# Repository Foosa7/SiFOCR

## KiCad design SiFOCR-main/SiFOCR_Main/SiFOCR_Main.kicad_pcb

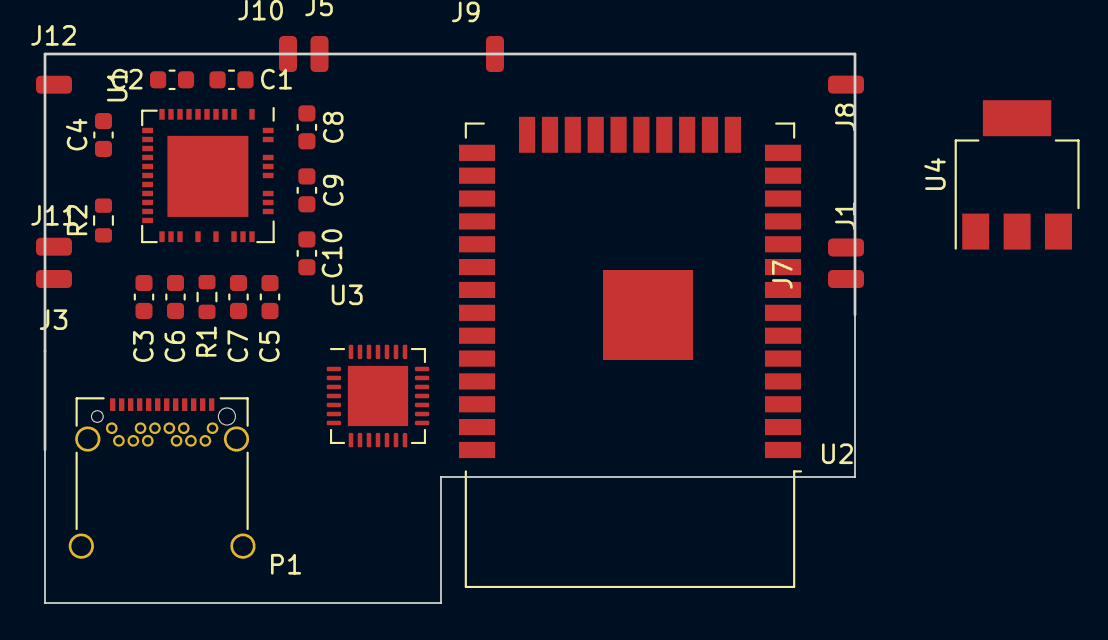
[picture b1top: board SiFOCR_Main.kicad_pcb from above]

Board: 4 copper layers, 45.0 x 30.5 mm, 26 parts (0 on the bottom side), 26 nets, no tracks yet.

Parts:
C1, C2: 2.2uF/50V; C_0603_1608Metric
C3, C7: 100nF/100V; C_0603_1608Metric
C4: 100nF/50V; C_0603_1608Metric
C5: 22nF/100V; C_0603_1608Metric
C6: C_Small; C_0603_1608Metric
C8, C9, C10: 470nF/16V; C_0603_1608Metric
J1, J3, J5, J7, J8, J9, J10, J11, J12: Conn_01x01_Male; SolderWirePad_1x01_SMD_1x2mm
P1: USB_C_Plug; USB_C_Receptacle_Amphenol_12401548E4-2A_CircularHoles
R1: 0E; R_0603_1608Metric
R2: R_Small_US; R_0603_1608Metric
U1: TMC6100
U2: ESP32-WROOM-32D; ESP32-WROOM-32
U3: CP2102N-Axx-xQFN28; QFN-28-1EP_5x5mm_P0.5mm_EP3.35x3.35mm
U4: AMS1117-3.3; SOT-223-3_TabPin2

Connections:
/5VOUT: C2.1, U1.7 (5VOUT)
/12VOUT: C1.1, U1.6 (12VOUT)
/+VCC_IO: C4.1, U1.16 (VCC_IO)
/+VCP: C7.2, U1.29 (VCP)
/+VM: C6.1, C7.1, R1.2, U1.28 (VS)
/VSA: C3.1, R1.1, U1.25 (VSA)
CU: C8.2, U1.1 (CU)
CV: C9.2, U1.35 (CV)
CW: C10.2, U1.30 (CW)
GND: C1.2, C2.2, C3.2, C4.2, C6.2, R2.1, U1.8 (GNDA), U1.PAD
HSU: J11.1, U1.37 (HSU)
HSV: J9.1, U1.34 (HSV)
HSW: J7.1, U1.31 (HSW)
LSU: J12.1, U1.5 (LSU)
LSV: J10.1, U1.4 (LSV)
LSW: J8.1, U1.3 (LSW)
unnamed: C5.1, U1.27 (CPI)
unnamed: C5.2, U1.26 (CPO)
unnamed: P1.A1 (GND), P1.A12 (GND), P1.B1 (GND), P1.B12 (GND)
unnamed: P1.A4 (VBUS), P1.A9 (VBUS), P1.B4 (VBUS), P1.B9 (VBUS)
unnamed: R2.2, U1.21 (CLK)
unnamed: U2.1 (GND), U2.15 (GND), U2.38 (GND), U2.39 (GND)
unnamed: U3.3 (GND), U3.29 (GND)
U: C8.1, J3.1, U1.36 (U)
V: C9.1, J5.1, U1.33 (V)
W: C10.1, J1.1, U1.32 (W)

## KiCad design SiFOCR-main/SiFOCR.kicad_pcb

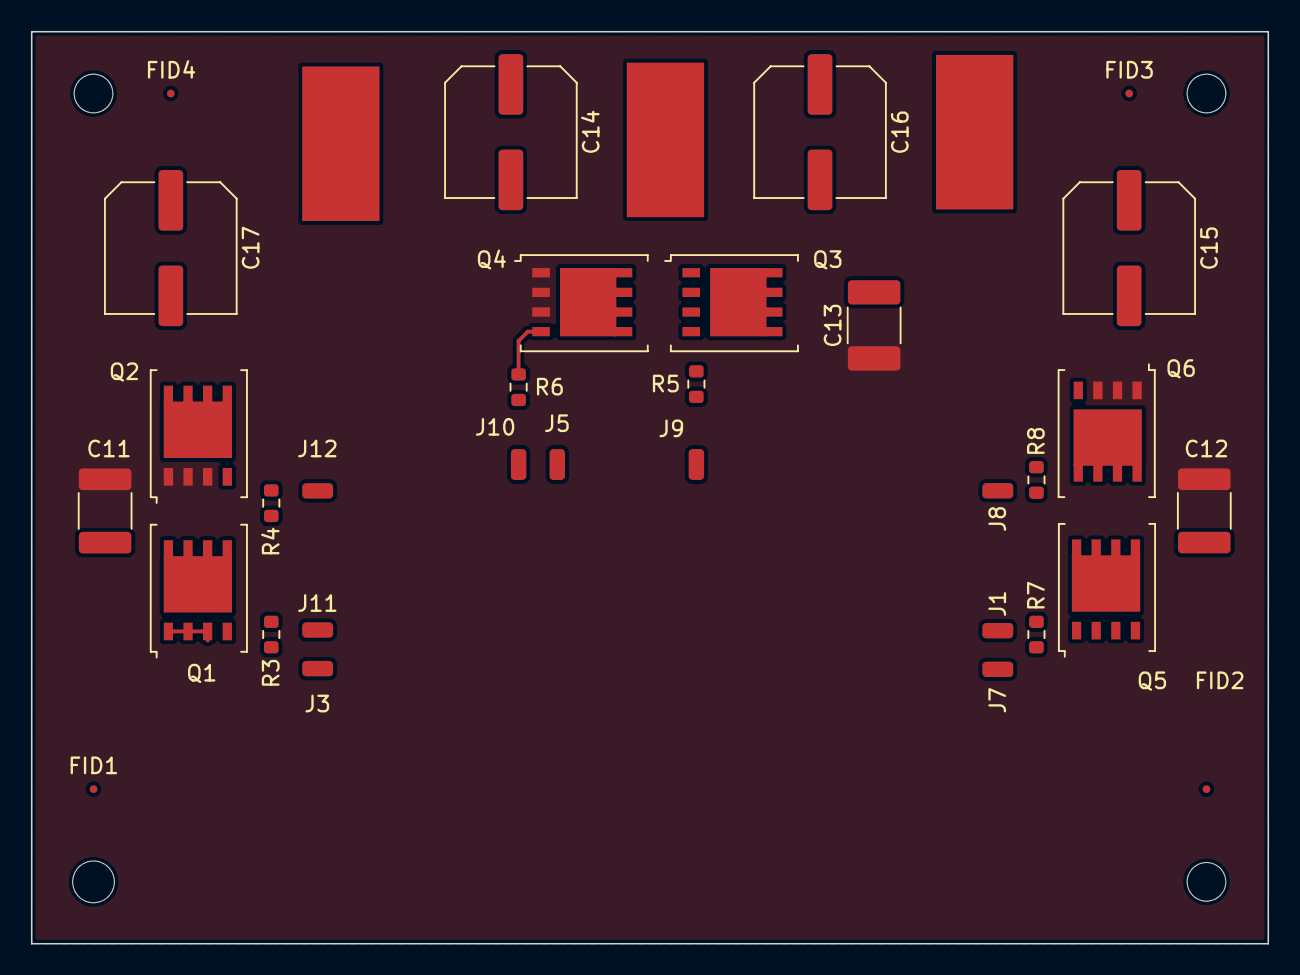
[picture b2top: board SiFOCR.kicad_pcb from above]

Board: 2 copper layers, 80.0 x 59.0 mm, 39 parts (0 on the bottom side), 17 nets.

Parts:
C11, C12: MotorC; C_1812_4532Metric
C13: MotorC; C_1812_4532Metric_Pad1.57x3.40mm_HandSolder
C14, C15, C16, C17: MotorC; C_Elec_8x5.4
FID1, FID2, FID3, FID4: Fiducial; Fiducial_0.5mm_Mask1mm
H1: MountingHole; MountingHole_2.7mm_M2.5
H2, H3, H4: MountingHole; MountingHole_2.5mm
J1, J3, J5, J7, J8, J9, J10, J11, J12: Conn_01x01_Male; SolderWirePad_1x01_SMD_1x2mm
J13, J14, J15: Conn_01x01_Male; SolderWirePad_1x01_SMD_5x10mm
Q1, Q2, Q3, Q4, Q5, Q6: IRFH5010PbF
R3, R4, R5, R6, R7, R8: R_Small_US; R_0603_1608Metric

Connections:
/Gate Driver/+VM: C11.2, C12.2, C13.2, Q1.5 (D), Q3.5 (D), Q5.5 (D)
GND: C11.1, C12.1, C13.1, Q2.1 (S), Q4.1 (S), Q6.1 (S)
HSU: J11.1, R3.1
HSV: J9.1, R5.1
HSW: J7.1, R7.1
LSU: J12.1, R4.1
LSV: J10.1, R6.1
LSW: J8.1, R8.1
unnamed: Q1.4 (G), R3.2
unnamed: Q2.4 (G), R4.2
unnamed: Q3.4 (G), R5.2
unnamed: Q4.4 (G), R6.2
unnamed: Q5.4 (G), R7.2
unnamed: Q6.4 (G), R8.2
U: J3.1, J14.1, Q1.1 (S), Q2.5 (D)
V: J5.1, J13.1, Q3.1 (S), Q4.5 (D)
W: J1.1, J15.1, Q5.1 (S), Q6.5 (D)
